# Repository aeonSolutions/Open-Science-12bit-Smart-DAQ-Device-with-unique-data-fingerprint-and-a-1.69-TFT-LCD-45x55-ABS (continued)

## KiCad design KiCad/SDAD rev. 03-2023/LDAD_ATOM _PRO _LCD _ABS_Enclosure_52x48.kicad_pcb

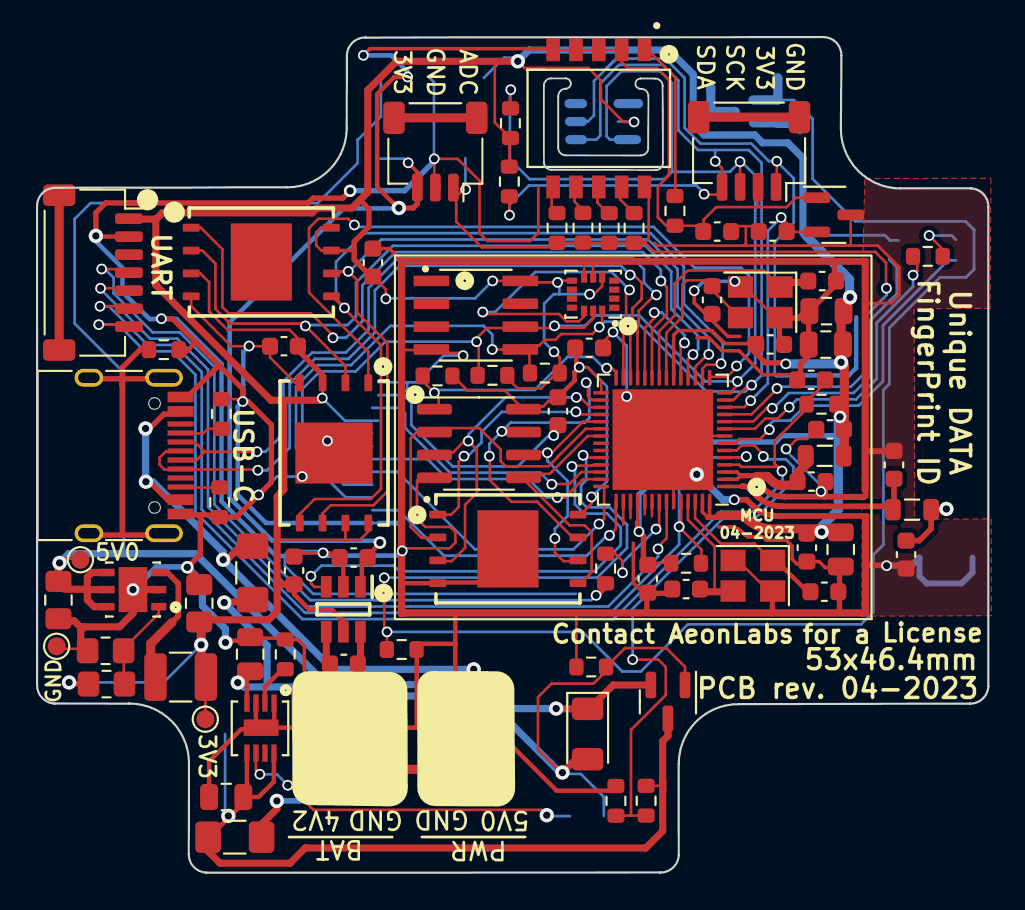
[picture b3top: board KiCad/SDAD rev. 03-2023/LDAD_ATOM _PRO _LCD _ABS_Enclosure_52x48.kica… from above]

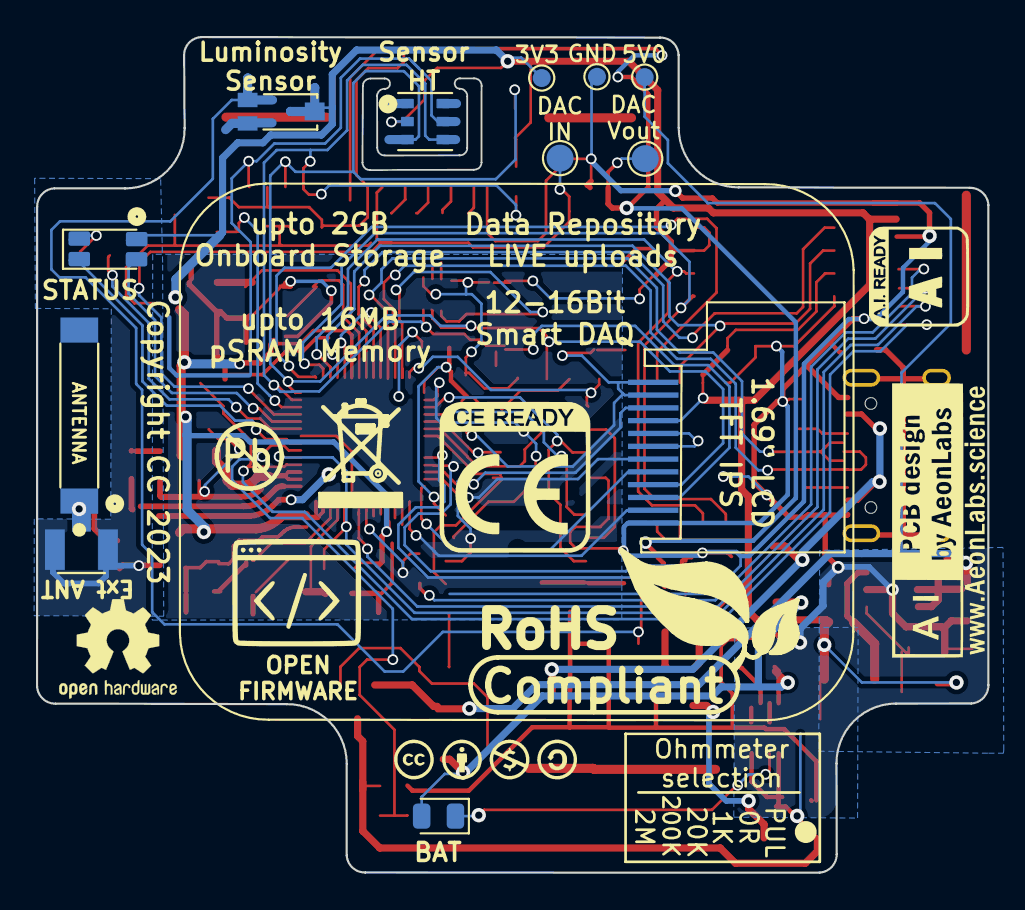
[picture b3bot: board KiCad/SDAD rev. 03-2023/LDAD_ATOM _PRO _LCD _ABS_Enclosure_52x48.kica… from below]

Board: 2 copper layers, 52.9 x 46.4 mm, 96 parts (13 on the bottom side), 66 nets.

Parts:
ATSHA_C1: 100nF; C_0603_1608Metric
AUR1: AUR9718x_DFN_3x3mm_6_pin; AUR9718 ST1S09 SON95P300X300X100-7N
AUR_C1: 22uF; C_0805_2012Metric_Pad1.18x1.45mm_HandSolder
AUR_C2: 4.7uF; C_0805_2012Metric_Pad1.18x1.45mm_HandSolder
AUR_R1: 24K; R_0805_2012Metric_Pad1.20x1.40mm_HandSolder
AUR_R2: 7k5; R_0805_2012Metric_Pad1.20x1.40mm_HandSolder
AUR_l1: 3.3uF; L_1210_3225Metric
BAT_FUSE1: Polyfuse; Fuse_1206_3216Metric_Pad1.42x1.75mm_HandSolder
BAT_SENSE_R1, BAT_SENSE_R2: 100k; R_0603_1608Metric
CN3065_C2: 4.7uF; C_0805_2012Metric
CN3065_R1: 1K8; R_0603_1608Metric
CN3065_STDBY_LED1: LED; LED_0805_2012Metric
CN3965_C1: 22uF; C_0805_2012Metric
DIPSW1: Conn_02x05_Odd_Even; Dip Switch 5pin 1mm SW_DS05-127-2-06BK-SMT-TR
DIP_R1: 4k7; R_0603_1608Metric
DIP_R2: 1k; R_0603_1608Metric
DIP_R3: 20k; R_0603_1608Metric
DIP_R4: 200k; R_0603_1608Metric
DIP_R5: 2M; R_0603_1608Metric
DMP1045U_1: DMP1045U; SOT-23
DMP1045_R1: 10K; R_0603_1608Metric
DMP1045_SCHOT1: D_Schottky; D_1206_3216Metric
EPS1: ESP32-PSRAM_LY68L6400S; SOIC-8_3.9x4.9mm_P1.27mm
ESP32S1: ESP32-S3; QFN-56-1EP_7x7mm_P0.4mm_EP5.6x5.6mm
ESP32_SHIELD1: RFShield_OnePiece; ESP32-S3 GND Shield
ESP_FLASH1, ESP_FLASH2, ESP_FLASH3: W25Q128JVS; WSON8 FLASH SPI SON127P800X600X80-9N
E_DTR_R1: 10k; R_0603_1608Metric
E_LNA_ANT1: AN9520; 2.4ghZ WIFI ANTENNA AN9520_ANT2-SMD-9.5X2.1X1.0MM
E_LNA_ANT2: U.FL-R-SMT(01); RF Antenna IPEX SMD PCB HRS_U.FL-R-SMT(01)
E_LNA_C1, E_LNA_C2: 2.7pF; C_0603_1608Metric
E_LNA_l1: 1.8nH 5%; L_0805_2012Metric
E_RTS_C1: 100nF; C_0603_1608Metric
E_RTS_R1: 10k; R_0603_1608Metric
E_SPI_C1: 1uF 10% 50V; C_0603_1608Metric
E_SPI_C2: 100nF 10% 16V; C_0603_1608Metric
E_UART_TX_1: 499R; R_0603_1608Metric
E_VDDA_C1: 100nF; C_0603_1608Metric
E_VDDA_C2: 1uF 10% 50V; C_0805_2012Metric
E_VDD_3_C1, E_VDD_3_C2: 10uF 20% 6.3V; C_0805_2012Metric
E_VDD_3_C3, E_VDD_3_C4: 100nF 10% 16V; C_0603_1608Metric
E_VDD_CPU_C1: 100nF 10% 16V; C_0603_1608Metric
E_VDD_L1: 12nH 5%; L_0805_2012Metric
E_VDD_RTC_C1: 100nF 10% 16V; C_0603_1608Metric
E_XTAL32_1: 32.768Mhz 22pF+-10PPM; Crystal_SMD_3225-4Pin_3.2x2.5mm
E_XTAL32_C1, E_XTAL32_C2, E_XTAL40_C1, E_XTAL40_C2: 22pF 5% 50V; C_0603_1608Metric
E_XTAL40_1: 40Mhz 22pF+-10PPM; Crystal_SMD_3225-4Pin_3.2x2.5mm
ExtSW1: Conn_01x03_Female; JST_SH_SM03B-SRSS-TB_1x03-1MP_P1.00mm_Horizontal
ExtSWBAT_PLUG2: Conn_01x03_Female; JST_SH_SM03B-SRSS-TB_1x03-1MP_P1.00mm_Horizontal
HX1: HX4002; HX4002 SOT95 P280X125-6N
HX_C1, HX_C2, HX_C3: 2.2uF; C_0603_1608Metric
I2C_PLUG1: I2C6; JST_SH_SM04B-SRSS-TB_1x04-1MP_P1.00mm_Horizontal
I2C_SCL_R1, I2C_SDA_R1: 10k; R_0603_1608Metric
IMR1, IMR2: 10K; R_0603_1608Metric
IMU1: LSM6DS3; LSM6DS3 Motion Sensor PQFN50P300X250X86-14N
J1: TYPE-C-31-M-12; USB_C_Receptacle_HRO_TYPE-C-31-M-12
JICSP1: Conn_01x07_Socket; JST_SH_SM07B-SRSS-TB_1x07-1MP_P1.00mm_Horizontal
LCD1: Conn_01x12_Male; 1,69 inch LCD IPS TFT
LED1: LED_GBRC; LED_1206_3210_RGB_Metric
LR1: 330R; R_0603_1608Metric
PSRAM_R1: 100K; R_0603_1608Metric
PWR_FUSE1: Polyfuse; Fuse_1206_3216Metric_Pad1.42x1.75mm_HandSolder
PWR_PLUG1: Screw_Terminal_01x02; JST_SH_SM02B-SRSS-TB_1x02-1MP_P1.00mm_Horizontal
SPI_STORAG_C1: 100nF; C_0603_1608Metric
Sign-PbFree: LOGO_PBFREE
Sign-RecycleBin: LOGO_RECYCLEBIN_1
Sign-RoHS: LOGO_ROHS_1
TMPR1: 10K; R_0603_1608Metric
TP1, TP1#2: VIN; TestPoint_Pad_D1.0mm
TP2, TP2#2: VOut; TestPoint_Pad_D1.0mm
TP3, TP3#2: GND; TestPoint_Pad_D1.0mm
U1: MCP1525-TT; SOT-23
U2: ATSHA204A-MAHDA-T; ATSHA204A Auth SOIC8
U3: Battery_charger_CN3065_QFN8; QFN8 3.1x2.9mm QFNn-8 3x3 SON80P400X400X100-9N
U4: AHT20; AHT20 HT Sensor PSON100P300X300X110-6N
U6: TEMT6000; TEMT6000-SEN
USB_PLUG_R1, USB_PLUG_R3: 5k1; R_0603_1608Metric
USB_PLYG_R2: 150K; R_0603_1608Metric
VOLTAGE_REF_C1, VOLTAGE_REF_C2: 100nF; C_0603_1608Metric

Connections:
3V3: ATSHA_C1.2, AUR_C1.1, AUR_R1.1, AUR_l1.1, ESP32S1.20 (VDD3P3_RTC), ESP32S1.46 (VDD3P3_CPU), ESP32S1.55 (VDDA), ESP32S1.56 (VDDA), ESP_FLASH2.3 (IO2), ESP_FLASH2.7 (IO3), ESP_FLASH2.8 (VCC), ESP_FLASH3.3 (IO2), ESP_FLASH3.7 (IO3), ESP_FLASH3.8 (VCC), E_DTR_R1.1, E_RTS_R1.1, E_VDDA_C1.2, E_VDDA_C2.2, E_VDD_3_C1.1, E_VDD_3_C2.1, E_VDD_3_C3.1, E_VDD_CPU_C1.1, E_VDD_L1.1, E_VDD_RTC_C1.1, HX1.5 (VIN), HX_C3.2, I2C_SCL_R1.1, I2C_SDA_R1.2, IMR1.1, IMR2.1, IMU1.5 (VDDIO), IMU1.8 (VDD), JICSP1.1, LCD1.4, LED1.4 (K), SPI_STORAG_C1.2, TP2.1, TP2#2.1, U2.8 (VCC), U4.2 (VDD), U6.COLLECTOR
3V3_PLUG: DIPSW1.3, DIPSW1.5, DIPSW1.7, DIPSW1.9, DIP_R1.2, ExtSW1.3, HX1.1 (VOUT), HX_C1.1, I2C_PLUG1.2, U1.1 (Vin), VOLTAGE_REF_C1.2
ADC_IN_IO04: DIPSW1.2, DIP_R2.1, DIP_R3.1, DIP_R4.1, DIP_R5.1, ESP32S1.11 (GPIO6/ADC1_CH5), ExtSW1.1
BAT_SENSE_IO21: BAT_SENSE_R1.1, BAT_SENSE_R2.2, ESP32S1.6 (GPIO1/ADC1_CH0)
CHIP_EN: ESP32S1.4 (CHIP_PU/RESET), E_RTS_C1.2, E_RTS_R1.2, JICSP1.7
DAC_CALIBRATION: ESP32S1.19 (GPIO14/ADC2_CH3), ESP32S1.24 (GPIO18/ADC2_CH7/DAC_1)
ESP_GPIO0_BOOT-DTR: ESP32S1.5 (GPIO0/BOOT), ESP32S1.52 (GPIO46), E_DTR_R1.2, JICSP1.6
FSPICLK_IO12: ESP32S1.17 (GPIO12/ADC2_CH1), ESP_FLASH2.6 (CLK), ESP_FLASH3.6 (CLK)
GND: ATSHA_C1.1, AUR1.2 (GND), AUR1.7 (GND), AUR_C1.2, AUR_C2.2, AUR_R2.2, BAT_SENSE_R1.2, CN3065_C2.1, CN3065_R1.1, CN3965_C1.1, DMP1045_R1.2, EPS1.4 (VSS), ESP32S1.8 (GPIO3/ADC1_CH2), ESP32S1.51 (GPIO45), ESP32S1.57 (GND), ESP32_SHIELD1.1 (Shield), ESP_FLASH1.4 (GND), ESP_FLASH1.9 (GND), ESP_FLASH2.4 (GND), ESP_FLASH3.4 (GND), E_LNA_ANT2.1 (GND), E_LNA_ANT2.2 (GND), E_LNA_C1.2, E_LNA_C2.2, E_RTS_C1.1, E_SPI_C1.2, E_SPI_C2.2, E_VDDA_C1.1, E_VDDA_C2.1, E_VDD_3_C1.2, E_VDD_3_C2.2, E_VDD_3_C3.2, E_VDD_3_C4.2, E_VDD_CPU_C1.2, E_VDD_RTC_C1.2, E_XTAL32_1.2, E_XTAL32_1.4, E_XTAL32_C1.2, E_XTAL32_C2.2, E_XTAL40_1.2, E_XTAL40_1.4, E_XTAL40_C1.2, E_XTAL40_C2.2, ExtSW1.2, ExtSWBAT_PLUG2.3, HX1.2 (GND), HX_C1.2, HX_C3.1, I2C_PLUG1.1, IMU1.6 (GND), IMU1.7 (GND), J1.B1, J1.B12 (A12), JICSP1.2, LCD1.1, LCD1.2, LCD1.5, LCD1.6, LCD1.12, PWR_PLUG1.1, SPI_STORAG_C1.1, TMPR1.1, TP3.1, TP3#2.1, U1.3 (Vss), U2.4 (GND), U3.1 (V_Temp), U3.3 (GND), U3.9 (GND), U4.5 (GND), USB_PLUG_R1.2, USB_PLUG_R3.2, USB_PLYG_R2.2, VOLTAGE_REF_C1.1, VOLTAGE_REF_C2.1
GPIO8_I2C_SDA: ESP32S1.13 (GPIO8/ADC1_CH7), I2C_PLUG1.4, I2C_SDA_R1.1, IMR1.2, IMU1.14 (SDA), LCD1.10, U2.5 (SDA), U4.4 (SDA)
GPIO9_I2C_SCL: ESP32S1.14 (GPIO9/ADC1_CH8), I2C_PLUG1.3, I2C_SCL_R1.2, IMR2.2, IMU1.13 (SCL), LCD1.9, U2.6 (SCL), U4.3 (SCL)
IMU_CS_IO21: ESP32S1.27 (GPIO21), IMU1.12 (CS)
LCD2_CS_IO37: ESP32S1.42 (GPIO37), LCD1.8
LCD2_DC_IO36: ESP32S1.41 (GPIO36), LCD1.7
LCD2_LED_IO35: ESP32S1.40 (GPIO35), LCD1.3
LCD2_RST_IO38: ESP32S1.43 (GPIO38), LCD1.11
LED_B_IO05: ESP32S1.10 (GPIO5/ADC1_CH4), LED1.2 (BA)
LED_G_IO02: ESP32S1.7 (GPIO2/ADC1_CH1), LED1.1 (GA)
LED_R_IO04: ESP32S1.9 (GPIO4/ADC1_CH3), LR1.1
unnamed: AUR1.1 (FB), AUR_R1.2, AUR_R2.1
unnamed: AUR1.3 (SW), AUR_l1.2
unnamed: DIPSW1.1, DIP_R1.1
unnamed: DIPSW1.4, DIP_R2.2
unnamed: DIPSW1.6, DIP_R3.2
unnamed: DIPSW1.8, DIP_R4.2
unnamed: DIPSW1.10, DIP_R5.2
unnamed: ESP32S1.21 (GPIO15/ADC2_CH4/XTAL_32K_P), E_XTAL32_1.3, E_XTAL32_C1.1
unnamed: ESP32S1.22 (GPIO16/ADC2_CH5/XTAL_32K_N), E_XTAL32_1.1, E_XTAL32_C2.1
unnamed: ESP32S1.1 (LNA_IN/RF), E_LNA_C2.1, E_LNA_l1.2
unnamed: ESP32S1.49 (U0TXD/PROG/GPIO43), E_UART_TX_1.2
unnamed: ESP32S1.2 (VDD3P3), ESP32S1.3 (VDD3P3), E_VDD_3_C4.1, E_VDD_L1.2
unnamed: ESP32S1.53 (XTAL_N), E_XTAL40_1.3, E_XTAL40_C2.1
unnamed: ESP32S1.54 (XTAL_P), E_XTAL40_1.1, E_XTAL40_C1.1
unnamed: E_LNA_ANT1.1, E_LNA_ANT2.3 (SIG), E_LNA_C1.1, E_LNA_l1.1
unnamed: HX1.6 (C+), HX_C2.1
unnamed: HX1.4 (C-), HX_C2.2
unnamed: J1.A5 (CC1), USB_PLUG_R3.1
unnamed: J1.B5 (CC2), USB_PLUG_R1.1
unnamed: J1.S1 (SHIELD), USB_PLYG_R2.1
unnamed: LED1.3 (RA), LR1.2
unnamed: CN3065_R1.2, U3.2 (I_SET)
PLUG_PWR_3V3_EN_IO38: ESP32S1.39 (GPIO34), HX1.3 (EN)
RXD0: ESP32S1.50 (U0RXD/PROG/GPIO44), JICSP1.5
SPICLK: EPS1.6 (SCLK), ESP32S1.33 (SPICLK/GPIO30), ESP_FLASH1.6 (CLK)
SPICS0: ESP32S1.32 (SPICS0/GPIO29), ESP_FLASH1.1 (~CS)
SPICS1: EPS1.1 (~CE), ESP32S1.28 (SPI_CS1/GPIO26), PSRAM_R1.1
SPID: EPS1.5 (SiO0), ESP32S1.35 (SPID/GPIO32), ESP_FLASH1.5 (DI(IO0))
SPIHD: EPS1.7 (SIO3), ESP32S1.30 (SPIHD/GPIO27), ESP_FLASH1.7 (IO3)
SPIQ: EPS1.2 (SIO1), ESP32S1.34 (SPIQ/GPIO31), ESP_FLASH1.2 (DO(IO1))
SPIWP: EPS1.3 (SIO2), ESP32S1.31 (SPIWP/GPIO28), ESP_FLASH1.3 (IO2)
STDBY_LED_G: CN3065_STDBY_LED1.1 (K), U3.6 (LED_DONE)
STORAGE_2_CS_IO17: ESP32S1.23 (GPIO17/ADC2_CH6/DAC_2), ESP_FLASH2.1 (~CS)
STORAGE_CS_IO10: ESP32S1.15 (GPIO10/ADC1_CH9), ESP_FLASH3.1 (~CS)
STORAGE_MISO_SPIQ_IO13: ESP32S1.18 (GPIO13/ADC2_CH2), ESP_FLASH2.2 (DO(IO1)), ESP_FLASH3.2 (DO(IO1))
STORAGE_MOSI_SPID_IO11: ESP32S1.16 (GPIO11/ADC2_CH0), ESP_FLASH2.5 (DI(IO0)), ESP_FLASH3.5 (DI(IO0))
TEMT6000_IO33: ESP32S1.38 (GPIO33), TMPR1.2, U6.EMITTER
TXD0: E_UART_TX_1.1, JICSP1.4
USB_5V0: CN3065_STDBY_LED1.2 (A), CN3965_C1.2, DMP1045U_1.1, DMP1045_R1.1, DMP1045_SCHOT1.2 (A), PWR_FUSE1.1, U3.4 (VIN)
USB_5V0F: J1.A9, J1.B4, PWR_FUSE1.2, PWR_PLUG1.2
USB_D+: ESP32S1.26 (GPIO20/USB_D+/ADC2_CH9), J1.A6 (DP1), J1.B6 (DP2)
USB_D-: ESP32S1.25 (GPIO19/USB_D-/ADC2_CH8), J1.A7 (DN1), J1.B7 (DN2)
VDD_SPI: EPS1.8 (VCC), ESP32S1.29 (VDD_SPI), ESP_FLASH1.8 (VCC), E_SPI_C1.1, E_SPI_C2.1, PSRAM_R1.2
VIN: AUR1.4 (VIN_SW), AUR1.5 (VIN_A), AUR1.6 (EN), AUR_C2.1, DMP1045U_1.2, DMP1045_SCHOT1.1 (K), TP1.1, TP1#2.1
VIN_BAT: BAT_FUSE1.1, BAT_SENSE_R2.1, CN3065_C2.2, DMP1045U_1.3, U3.5 (BAT+), U3.8 (FB)
VIN_BATF: BAT_FUSE1.2, ExtSWBAT_PLUG2.1
VOLTAGE_REF_IO07: ESP32S1.12 (GPIO7/ADC1_CH6), U1.2 (Vout), VOLTAGE_REF_C2.2
